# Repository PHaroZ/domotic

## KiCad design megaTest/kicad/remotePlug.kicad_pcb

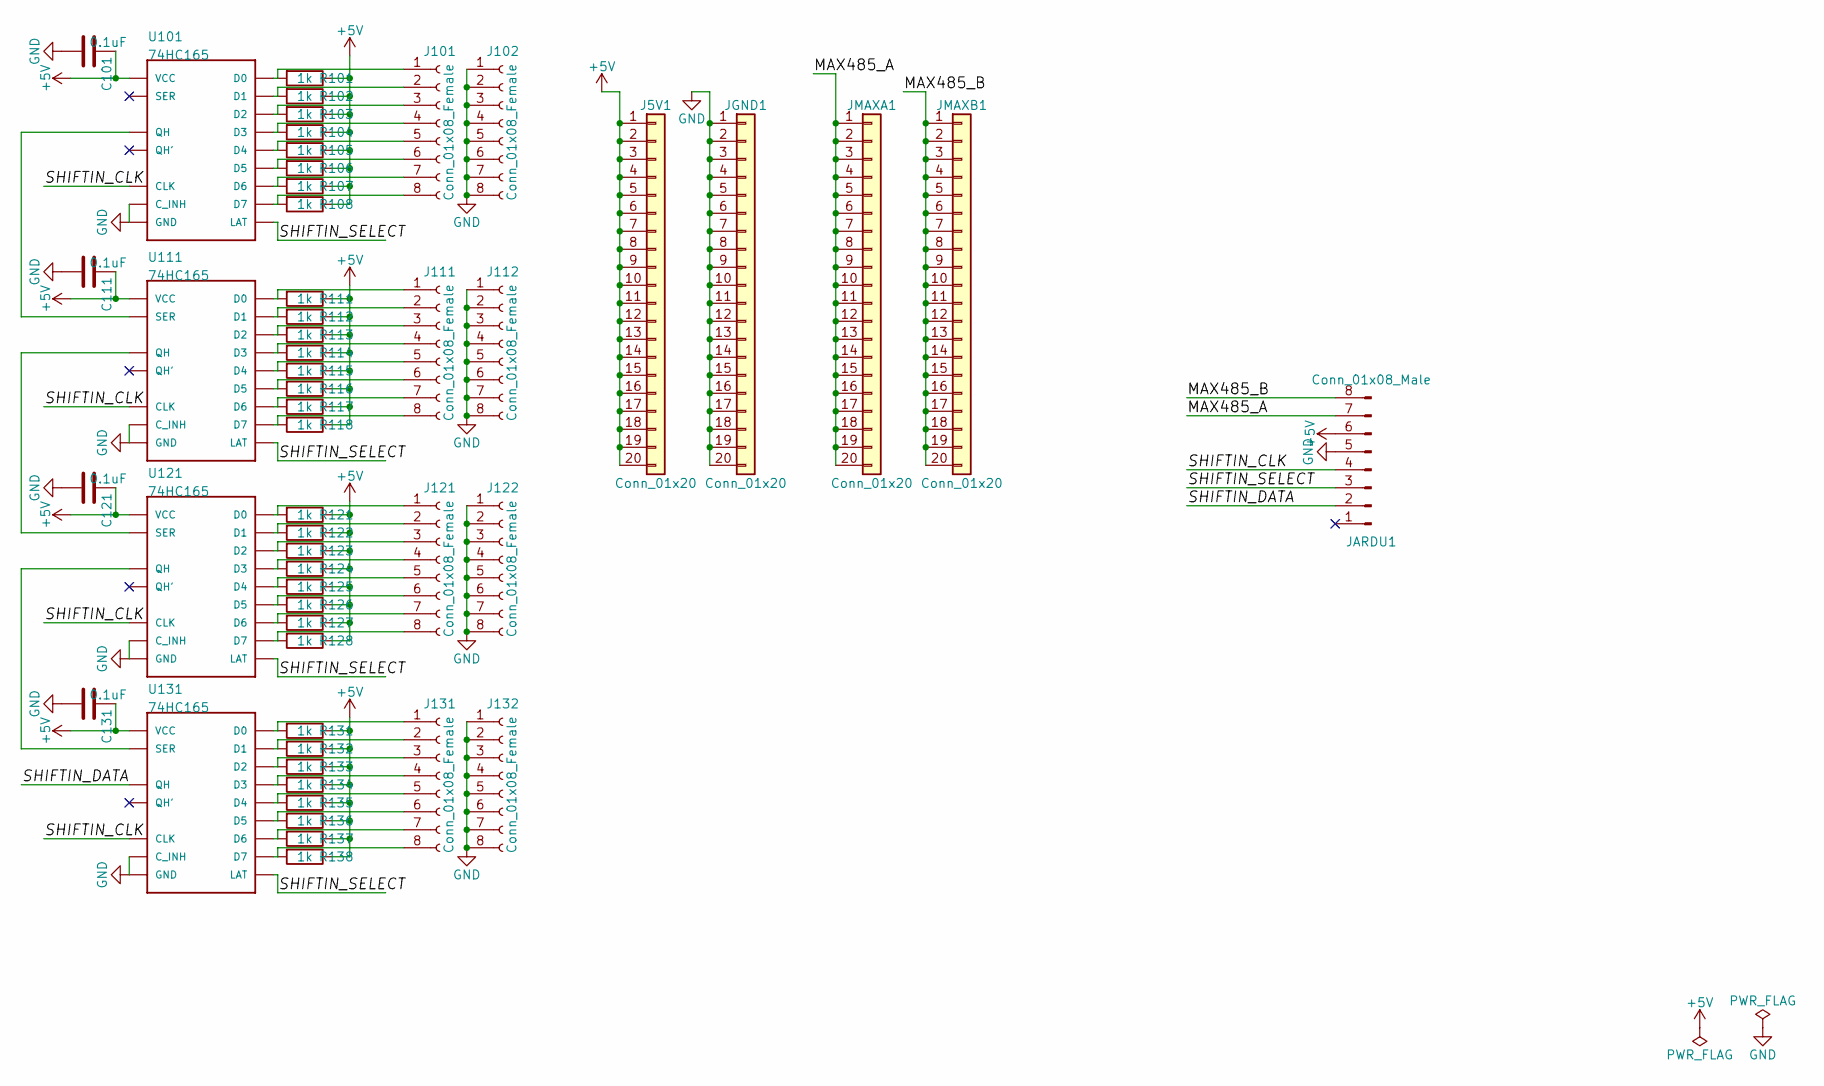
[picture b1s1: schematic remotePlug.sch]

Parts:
C101, C111, C121, C131: 0.1uF; C_Disc_D3.0mm_W2.0mm_P2.50mm
J5V1: Conn_01x20; Socket_Strip_Straight_1x20_Pitch2.54mm
J101, J102, J111, J112, J121, J122, J131, J132: Conn_01x08_Female; Socket_Strip_Straight_1x08_Pitch2.54mm
JARDU1: Conn_01x08_Male; Pin_Header_Straight_1x08_Pitch2.54mm
JGND1: Conn_01x20; Socket_Strip_Straight_1x20_Pitch2.54mm
JMAXA1: Conn_01x20; Pin_Header_Straight_1x20_Pitch2.54mm
JMAXB1: Conn_01x20; Pin_Header_Straight_1x20_Pitch2.54mm
R101, R102, R103, R104, R105, R106, R107, R108, R111, R112, R113, R114, R115, R116, R117, R118, R121, R122, R123, R124, R125, R126, R127, R128, R131, R132, R133, R134, R135, R136, R137, R138: 1k; R_Axial_DIN0207_L6.3mm_D2.5mm_P10.16mm_Horizontal
U101, U111, U121, U131: 74HC165; DIP-16_W7.62mm

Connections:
+5V: C101.1, C111.1, C121.1, C131.1, J5V1.1, J5V1.2, J5V1.3, J5V1.4, J5V1.5, J5V1.6, J5V1.7, J5V1.8, J5V1.9, J5V1.10, J5V1.11, J5V1.12, J5V1.13, J5V1.14, J5V1.15, J5V1.16, J5V1.17, J5V1.18, J5V1.19, J5V1.20, JARDU1.6, R101.1, R102.1, R103.1, R104.1, R105.1, R106.1, R107.1, R108.1, R111.1, R112.1, R113.1, R114.1, R115.1, R116.1, R117.1, R118.1, R121.1, R122.1, R123.1, R124.1, R125.1, R126.1, R127.1, R128.1, R131.1, R132.1, R133.1, R134.1, R135.1, R136.1, R137.1, R138.1, U101.16 (VCC), U111.16 (VCC), U121.16 (VCC), U131.16 (VCC)
/MAX485_A: JARDU1.7, JMAXA1.1, JMAXA1.2, JMAXA1.3, JMAXA1.4, JMAXA1.5, JMAXA1.6, JMAXA1.7, JMAXA1.8, JMAXA1.9, JMAXA1.10, JMAXA1.11, JMAXA1.12, JMAXA1.13, JMAXA1.14, JMAXA1.15, JMAXA1.16, JMAXA1.17, JMAXA1.18, JMAXA1.19, JMAXA1.20
/MAX485_B: JARDU1.8, JMAXB1.1, JMAXB1.2, JMAXB1.3, JMAXB1.4, JMAXB1.5, JMAXB1.6, JMAXB1.7, JMAXB1.8, JMAXB1.9, JMAXB1.10, JMAXB1.11, JMAXB1.12, JMAXB1.13, JMAXB1.14, JMAXB1.15, JMAXB1.16, JMAXB1.17, JMAXB1.18, JMAXB1.19, JMAXB1.20
/SHIFTIN_CLK: JARDU1.4, U101.2 (CLK), U111.2 (CLK), U121.2 (CLK), U131.2 (CLK)
/SHIFTIN_DATA: JARDU1.2, U131.9 (QH)
/SHIFTIN_SELECT: JARDU1.3, U101.1 (LAT), U111.1 (LAT), U121.1 (LAT), U131.1 (LAT)
GND: C101.2, C111.2, C121.2, C131.2, J102.1, J102.2, J102.3, J102.4, J102.5, J102.6, J102.7, J102.8, J112.1, J112.2, J112.3, J112.4, J112.5, J112.6, J112.7, J112.8, J122.1, J122.2, J122.3, J122.4, J122.5, J122.6, J122.7, J122.8, J132.1, J132.2, J132.3, J132.4, J132.5, J132.6, J132.7, J132.8, JARDU1.5, JGND1.1, JGND1.2, JGND1.3, JGND1.4, JGND1.5, JGND1.6, JGND1.7, JGND1.8, JGND1.9, JGND1.10, JGND1.11, JGND1.12, JGND1.13, JGND1.14, JGND1.15, JGND1.16, JGND1.17, JGND1.18, JGND1.19, JGND1.20, U101.8 (GND), U101.15 (C_INH), U111.8 (GND), U111.15 (C_INH), U121.8 (GND), U121.15 (C_INH), U131.8 (GND), U131.15 (C_INH)
unnamed: J101.1, R101.2, U101.11 (D0)
unnamed: J101.2, R102.2, U101.12 (D1)
unnamed: J101.3, R103.2, U101.13 (D2)
unnamed: J101.4, R104.2, U101.14 (D3)
unnamed: J101.5, R105.2, U101.3 (D4)
unnamed: J101.6, R106.2, U101.4 (D5)
unnamed: J101.7, R107.2, U101.5 (D6)
unnamed: J101.8, R108.2, U101.6 (D7)
unnamed: J111.1, R111.2, U111.11 (D0)
unnamed: J111.2, R112.2, U111.12 (D1)
unnamed: J111.3, R113.2, U111.13 (D2)
unnamed: J111.4, R114.2, U111.14 (D3)
unnamed: J111.5, R115.2, U111.3 (D4)
unnamed: J111.6, R116.2, U111.4 (D5)
unnamed: J111.7, R117.2, U111.5 (D6)
unnamed: J111.8, R118.2, U111.6 (D7)
unnamed: J121.1, R121.2, U121.11 (D0)
unnamed: J121.2, R122.2, U121.12 (D1)
unnamed: J121.3, R123.2, U121.13 (D2)
unnamed: J121.4, R124.2, U121.14 (D3)
unnamed: J121.5, R125.2, U121.3 (D4)
unnamed: J121.6, R126.2, U121.4 (D5)
unnamed: J121.7, R127.2, U121.5 (D6)
unnamed: J121.8, R128.2, U121.6 (D7)
unnamed: J131.1, R131.2, U131.11 (D0)
unnamed: J131.2, R132.2, U131.12 (D1)
unnamed: J131.3, R133.2, U131.13 (D2)
unnamed: J131.4, R134.2, U131.14 (D3)
unnamed: J131.5, R135.2, U131.3 (D4)
unnamed: J131.6, R136.2, U131.4 (D5)
unnamed: J131.7, R137.2, U131.5 (D6)
unnamed: J131.8, R138.2, U131.6 (D7)
unnamed: U101.9 (QH), U111.10 (SER)
unnamed: U111.9 (QH), U121.10 (SER)
unnamed: U121.9 (QH), U131.10 (SER)

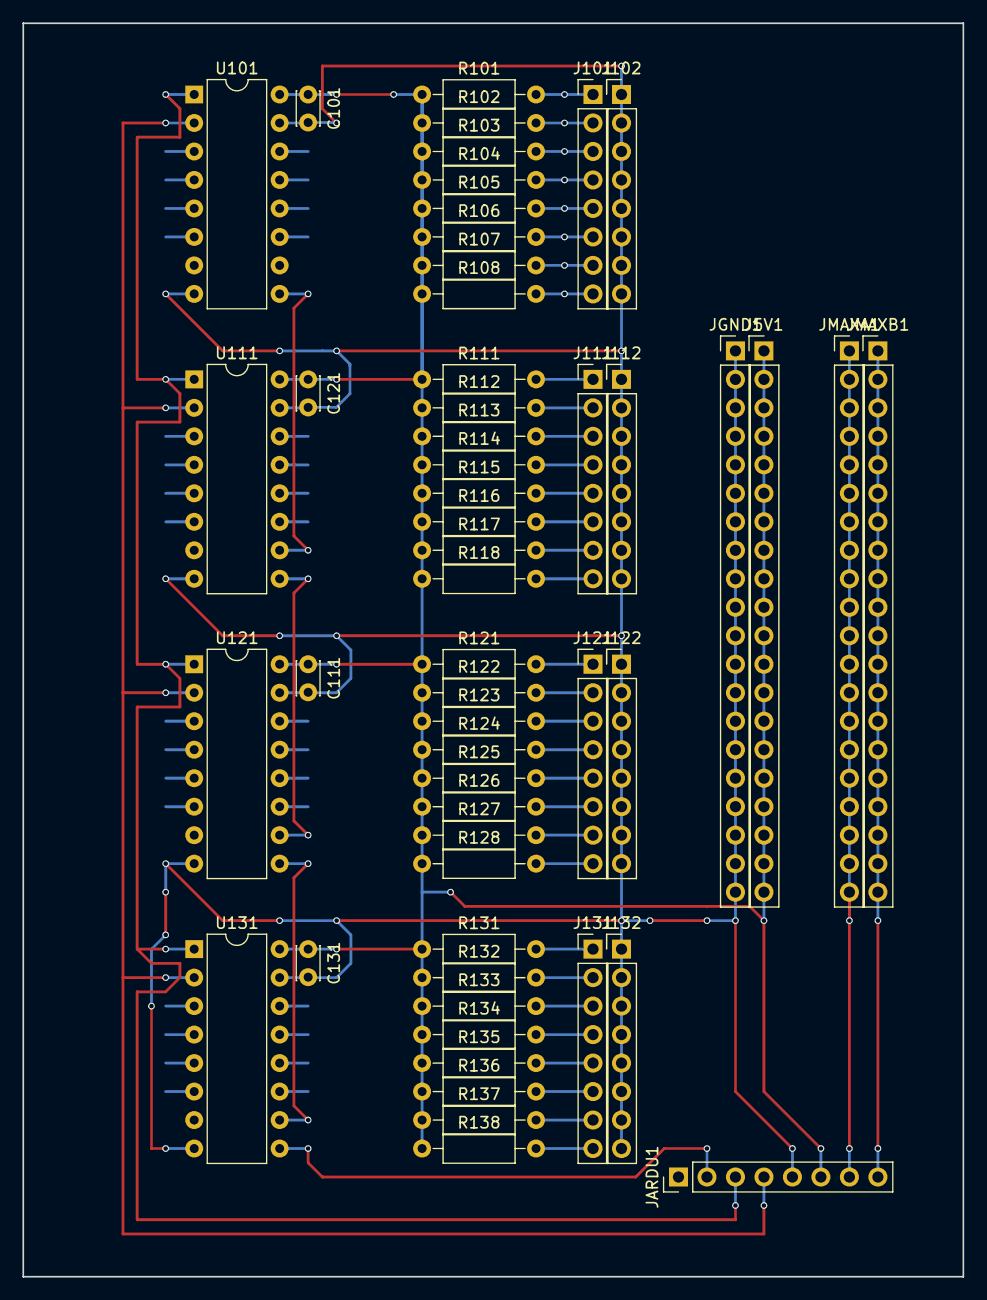
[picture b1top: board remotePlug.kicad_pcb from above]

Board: 2 copper layers, 83.8 x 111.8 mm, 53 parts (0 on the bottom side), 42 nets.

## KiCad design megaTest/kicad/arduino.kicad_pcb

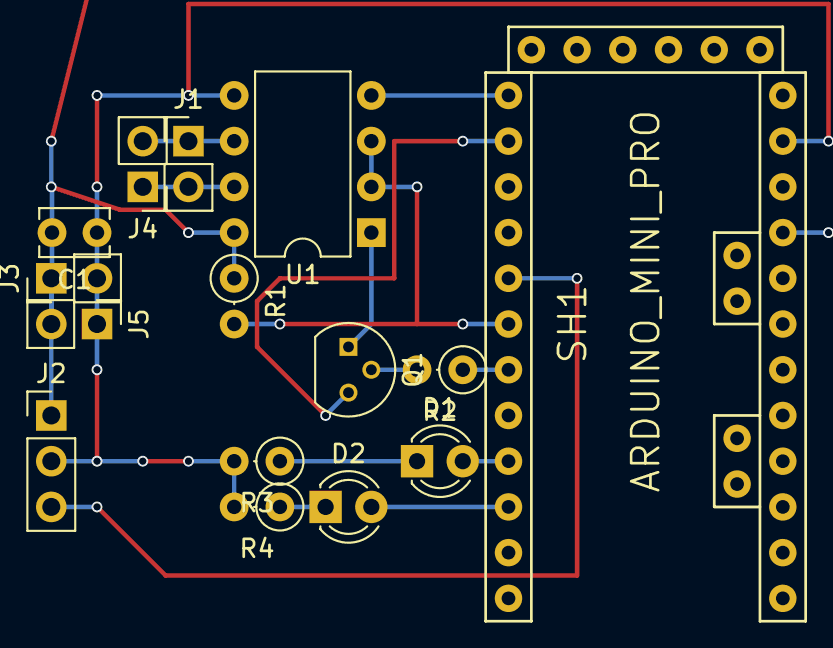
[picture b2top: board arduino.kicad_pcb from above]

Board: 2 copper layers, 15 parts (0 on the bottom side), 15 nets.

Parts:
C1: 0.1uF; C_Disc_D3.8mm_W2.6mm_P2.50mm
D1, D2: LED; LED_D3.0mm
J1: MAX485AB; Pin_Header_Straight_1x02_Pitch2.54mm
J2: RF module; Pin_Header_Straight_1x03_Pitch2.54mm
J3: POWER; Pin_Header_Straight_1x02_Pitch2.54mm
J4: MAX485AB_FW; Socket_Strip_Straight_1x02_Pitch2.54mm
J5: POWER_FW; Socket_Strip_Straight_1x02_Pitch2.54mm
Q1: BC547; TO-92_Molded_Narrow
R1: 4.7k; R_Axial_DIN0207_L6.3mm_D2.5mm_P2.54mm_Vertical
R2: 10k; R_Axial_DIN0207_L6.3mm_D2.5mm_P2.54mm_Vertical
R3, R4: 330; R_Axial_DIN0207_L6.3mm_D2.5mm_P2.54mm_Vertical
SH1: ARDUINO_MINI_PRO; ARDUINO_MINI_PRO_V10
U1: MAX485E; DIP-8_W7.62mm

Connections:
+5V: C1.2, J2.1, J3.1, J5.2, R1.1, SH1.VCC2, U1.8
/ArduinoRX: Q1.3, SH1.RX/2
/MAX485A: J1.1, J4.2, U1.6
/MAX485B: J1.2, J4.1, U1.7
/RFData: J2.3, SH1.2
GND: C1.1, J2.2, J3.2, J5.1, R3.2, R4.2, SH1.GND3, U1.5
unnamed: D1.1, R3.1
unnamed: D1.2, SH1.6
unnamed: D2.1, R4.1
unnamed: D2.2, SH1.7
unnamed: Q1.1, U1.1
unnamed: Q1.2, R2.2
unnamed: R1.2, SH1.3, U1.2, U1.3
unnamed: R2.1, SH1.4
unnamed: SH1.TX/2, U1.4

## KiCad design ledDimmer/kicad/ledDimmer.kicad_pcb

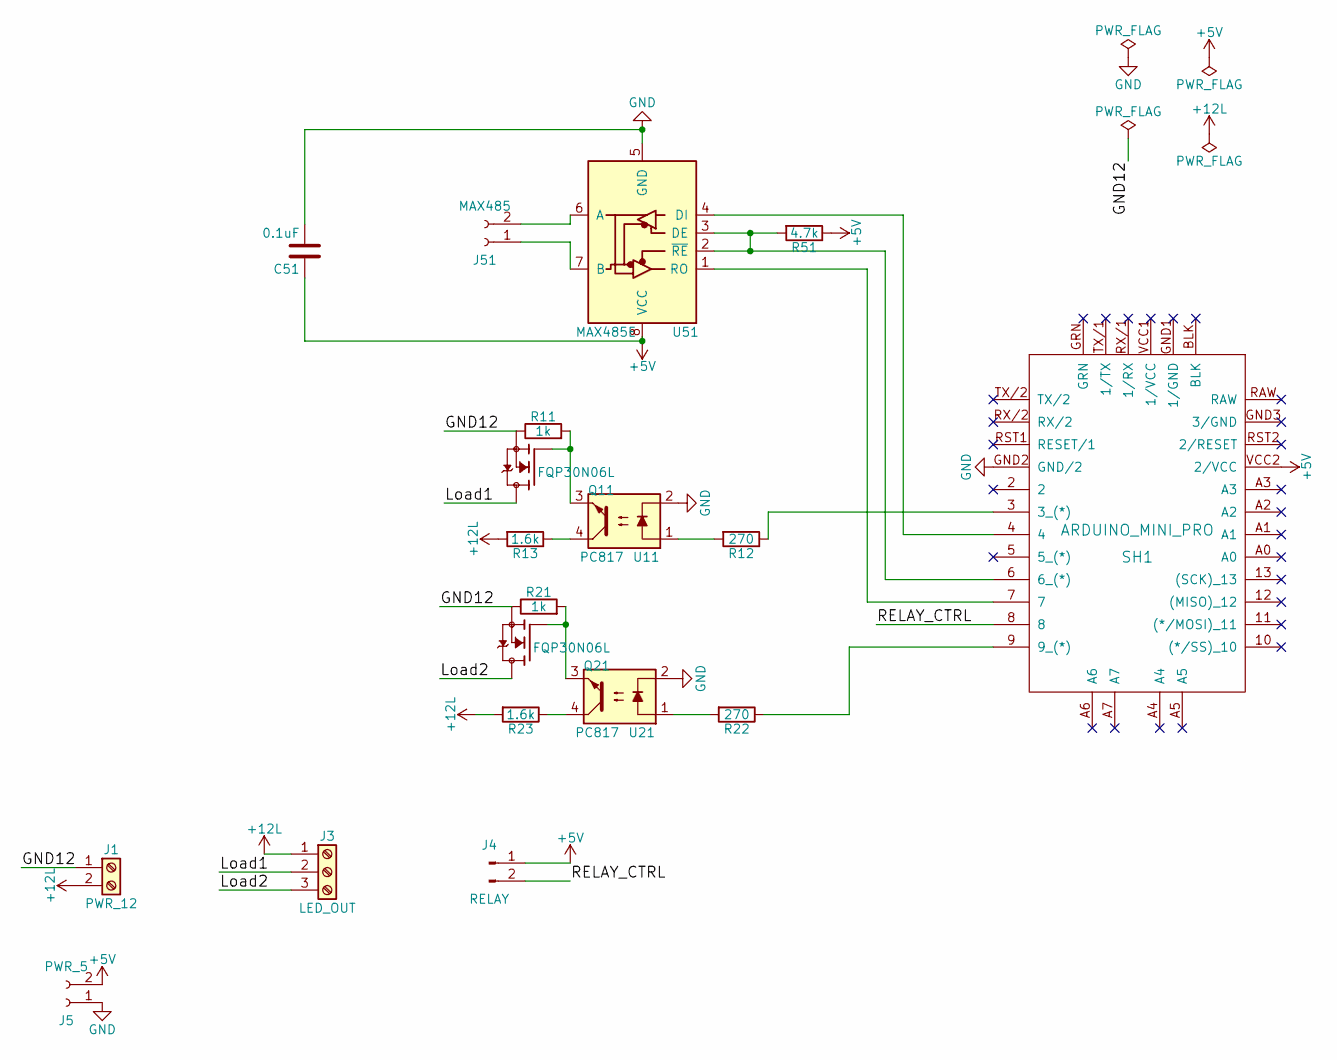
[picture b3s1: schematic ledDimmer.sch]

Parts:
C51: 0.1uF; C_Disc_D3.8mm_W2.6mm_P2.50mm
J1: PWR_12; TerminalBlock_Pheonix_MKDS1.5-2pol
J3: LED_OUT; TerminalBlock_Pheonix_MKDS1.5-3pol
J4: RELAY; Pin_Header_Straight_1x02_Pitch2.54mm
J5: PWR_5; Socket_Strip_Straight_1x02_Pitch2.54mm
J51: MAX485; Socket_Strip_Straight_1x02_Pitch2.54mm
Q11, Q21: FQP30N06L; TO-220_Vertical
R11, R21: 1k; R_Axial_DIN0207_L6.3mm_D2.5mm_P2.54mm_Vertical
R12, R22: 270; R_Axial_DIN0207_L6.3mm_D2.5mm_P2.54mm_Vertical
R13, R23: 1.6k; R_Axial_DIN0207_L6.3mm_D2.5mm_P2.54mm_Vertical
R51: 4.7k; R_Axial_DIN0207_L6.3mm_D2.5mm_P10.16mm_Horizontal
SH1: ARDUINO_MINI_PRO; ARDUINO_MINI_PRO_V10
U11, U21: PC817; DIP-4_W7.62mm
U51: MAX485E; DIP-8_W7.62mm

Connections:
+5V: C51.1, J4.1, J5.2, R51.1, SH1.VCC2 (2/VCC), U51.8 (VCC)
+12L: J1.2, J3.1, R13.2, R23.2
/GND12: J1.1, Q11.3 (S), Q21.3 (S), R11.1, R21.1
/Load1: J3.2, Q11.2 (D)
/Load2: J3.3, Q21.2 (D)
/RELAY_CTRL: J4.2, SH1.8
GND: C51.2, J5.1, SH1.GND2 (GND/2), U11.2, U21.2, U51.5 (GND)
unnamed: J51.1, U51.7 (B)
unnamed: J51.2, U51.6 (A)
unnamed: Q11.1 (G), R11.2, U11.3
unnamed: Q21.1 (G), R21.2, U21.3
unnamed: R12.1, SH1.3 (3_(*))
unnamed: R12.2, U11.1
unnamed: R13.1, U11.4
unnamed: R22.1, SH1.9 (9_(*))
unnamed: R22.2, U21.1
unnamed: R23.1, U21.4
unnamed: R51.2, SH1.6 (6_(*)), U51.2 (~RE), U51.3 (DE)
unnamed: SH1.4, U51.4 (DI)
unnamed: SH1.7, U51.1 (RO)

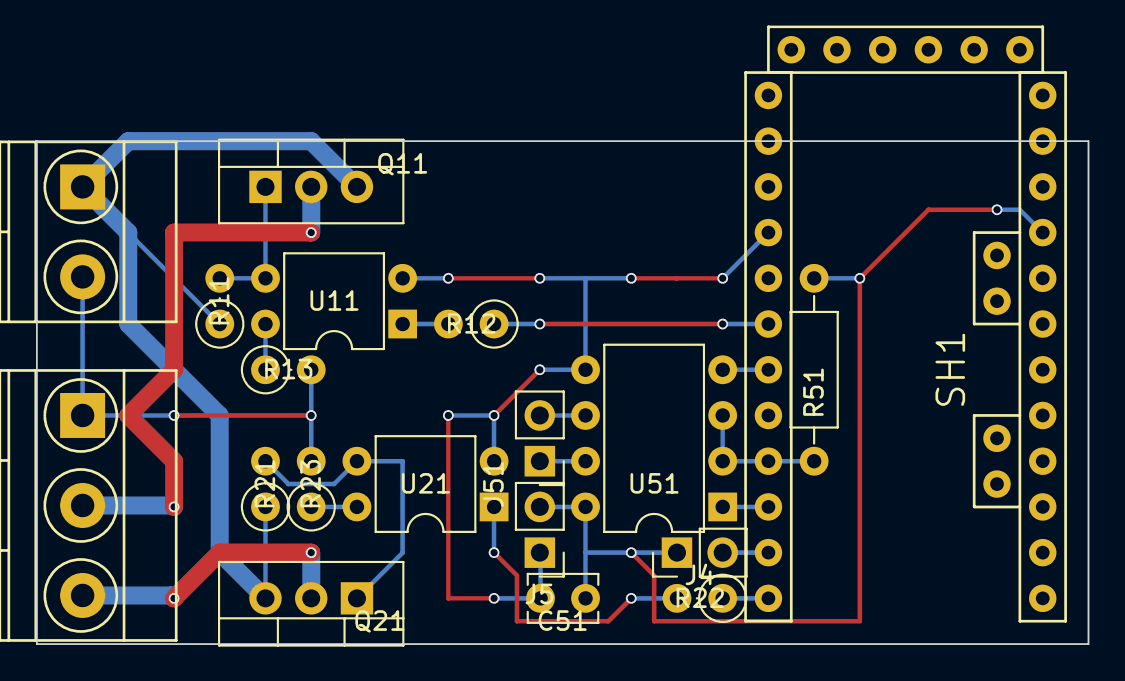
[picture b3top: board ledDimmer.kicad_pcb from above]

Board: 2 copper layers, 58.4 x 27.9 mm, 19 parts (0 on the bottom side), 20 nets.

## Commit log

2017-09-26 re join repo
2017-09-26 integrate new version of SNAP
2017-09-27 separate code in multiple class
2017-09-29 add management of acutors
2017-09-30 code refactoring, agin ...
2017-10-02 code refactoring
2017-10-06 add MySensors support
2017-10-09 MySensors integration in progress
2017-10-15 MySensors integration in progress2
2017-10-16 finish mySensors integration + bug fix in Orchestrator#onSwitchChange
2017-10-29 add temp support to rfReceiver
2017-10-30 remove support of temperature sensor
    (not compatibile with rcSwitch)
2017-10-30 reorganize configuration
2017-11-01 change pin number
2017-11-01 add kicad schemas
2017-11-01 update kicad schema
2017-11-05 add first draw of kicad schema for megaTest
2017-11-11 rfReceiver : add new buttons mapping
2017-11-20 mega : kicad schemas update
2017-11-21 megatTest : kicad svg format
